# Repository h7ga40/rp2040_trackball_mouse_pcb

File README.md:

# PCB for Kensington trackball with RP2040

[Kensington Orbit Trackball with Scroll Ring](https://www.kensington.com/p/products/electronic-control-solutions/trackball-products/orbit-trackball-with-scroll-ring/)の基板を[PGA2040](https://shop.pimoroni.com/products/pga2040)を使っ基板に置き換えるためのKiCadプロジェクト

## 基板発注時の注意

板厚は**1.2mm**です。

## 主要部品

|部品|入手先|備考|
|-|-|-|
|PGA2040|<https://akizukidenshi.com/catalog/g/gM-16762/>|Raspberry pi picoと同じCPU|
|IR928-6C-F|<https://www.marutsu.co.jp/pc/i/12907560/>|ホイール用２相エンコーダのLED</br>見た目が同じなので選択|
|PT5529B/L2/H3|<https://www.marutsu.co.jp/pc/i/13719542/>|ホイール用２相エンコーダのフォトトランジスタ</br>見た目が同じなので選択|
|LMV393D|<https://www.marutsu.co.jp/pc/i/30637519/>|２相エンコーダ信号用のコンパレータ|
|B6B-PH-K-S|<https://www.marutsu.co.jp/pc/i/46628/>|ADNS-5050との接続用コネクタ|
|S5B-PH-K-S|<https://www.marutsu.co.jp/pc/i/54957/>|USBケーブルとの接続用コネクタ|
|kailh mute switch|<https://www.amazon.co.jp/s?k=kailh+mute+switch>|マウスボタン</br>[秋月のタクトスイッチ](https://akizukidenshi.com/catalog/g/gP-14892/)で代用（1.6mm(7.3mm-5.7mm)の底上げが必要）|
|タクトスイッチ|<https://akizukidenshi.com/catalog/g/gP-06184/>|RP2040のリセットとモード選択用|

## ソフトウェア

[こちら](https://github.com/h7ga40/rp2040_trackball_mouse)にソフトウェアがあります。

## 部品実装

PGA2040周辺はこのような感じ

## その他の情報

[コネクテッド・マウス](https://www.slideshare.net/HiroakiNagashima1/ss-250643168)

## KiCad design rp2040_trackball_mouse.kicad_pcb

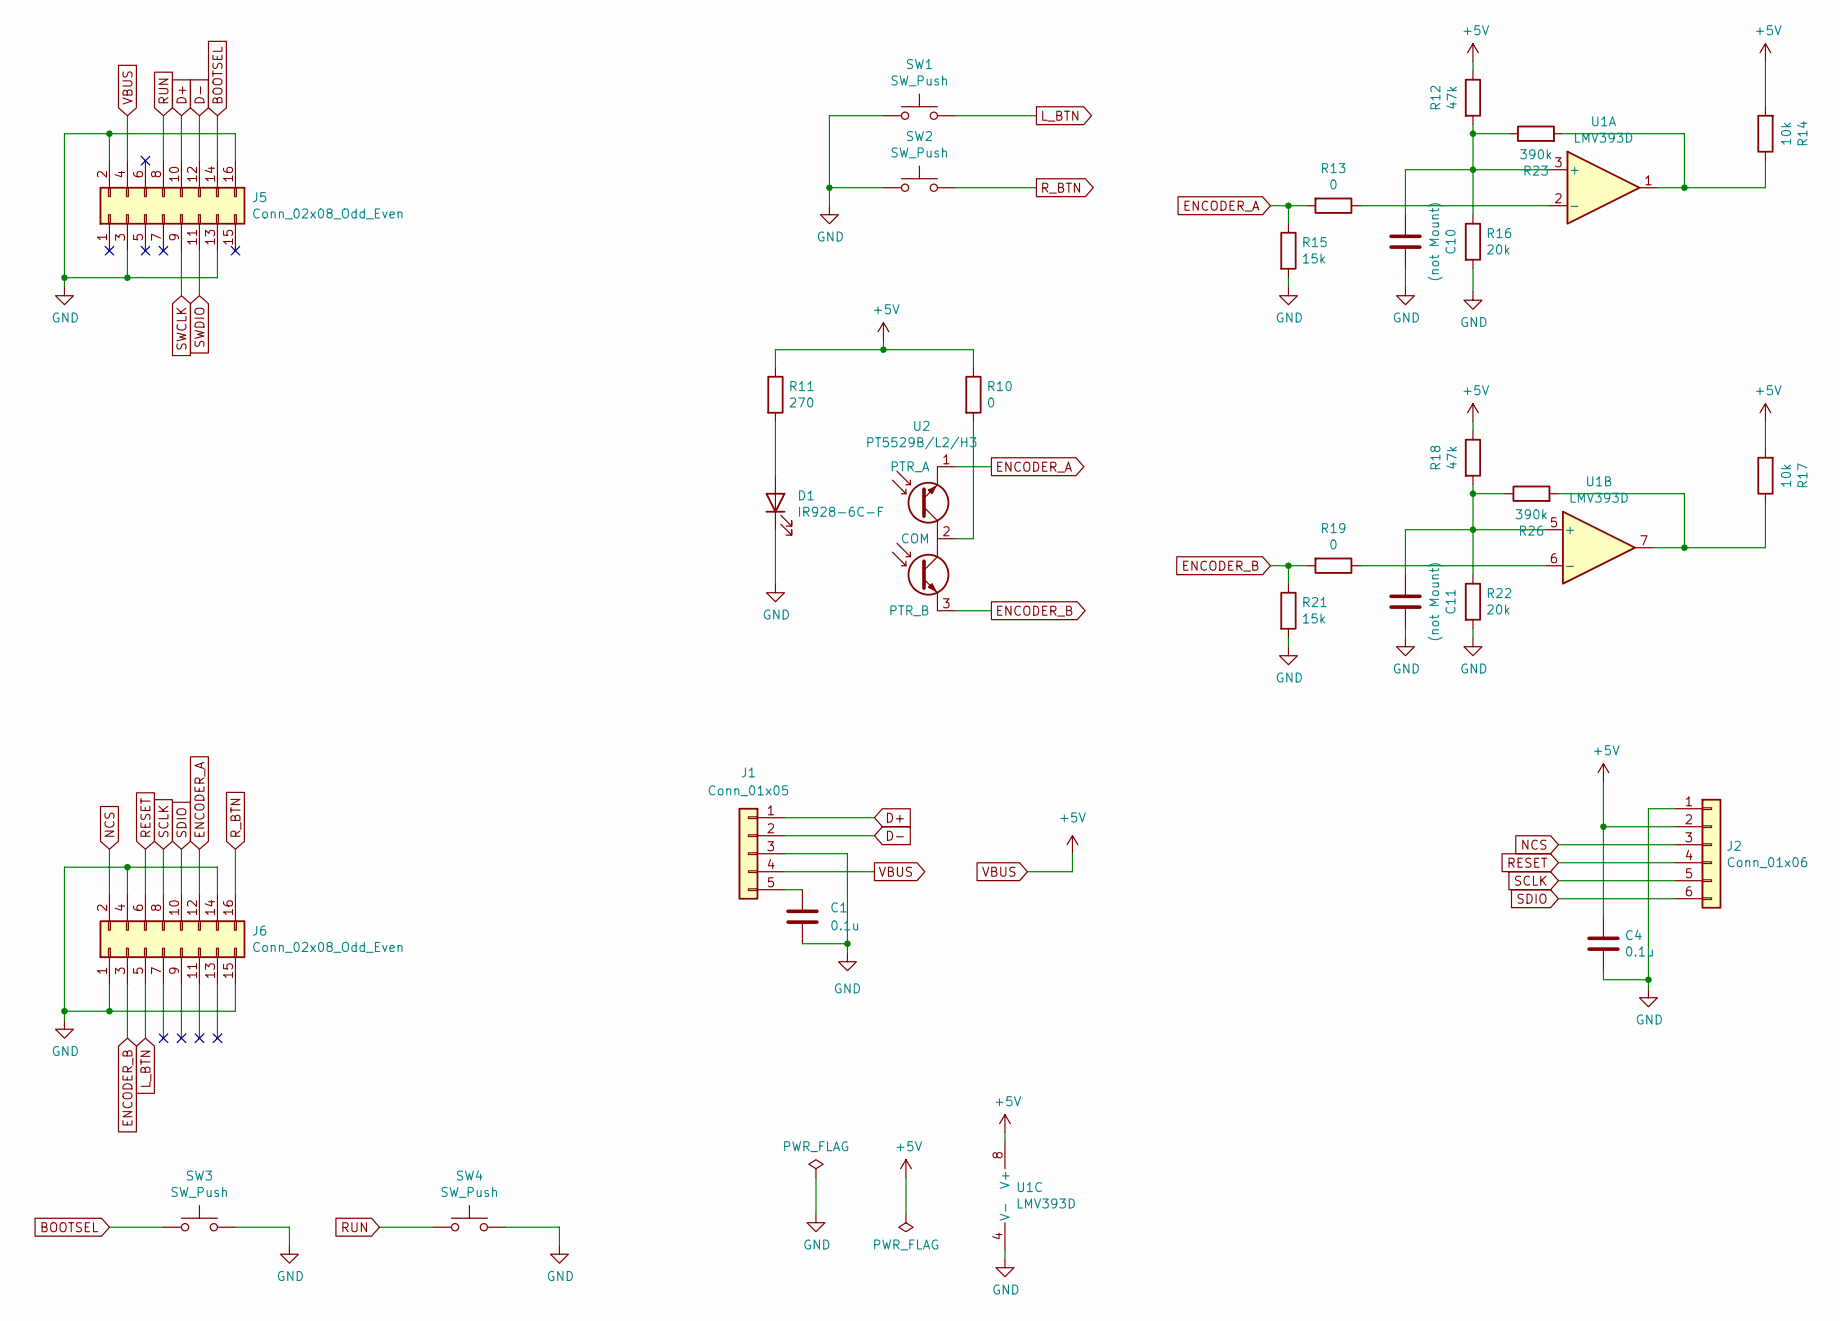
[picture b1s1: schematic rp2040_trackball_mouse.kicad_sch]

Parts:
C1, C4: 0.1u; C_0603_1608Metric_Pad1.08x0.95mm_HandSolder
C10, C11: (not Mount); C_0603_1608Metric_Pad1.08x0.95mm_HandSolder
D1: IR928-6C-F; LED_D2.0mm_W4.8mm_H2.5mm_FlatTop
J1: Conn_01x05; JST_PH_S5B-PH-K_1x05_P2.00mm_Horizontal
J2: Conn_01x06; JST_PH_B6B-PH-K_1x06_P2.00mm_Vertical
J5, J6: Conn_02x08_Odd_Even; PinHeader_2x08_P2.54mm_Vertical
R10, R13, R19: 0; R_0603_1608Metric_Pad0.98x0.95mm_HandSolder
R11: 270; R_0603_1608Metric_Pad0.98x0.95mm_HandSolder
R12, R18: 47k; R_0603_1608Metric_Pad0.98x0.95mm_HandSolder
R14, R17: 10k; R_0603_1608Metric_Pad0.98x0.95mm_HandSolder
R15, R21: 15k; R_0603_1608Metric_Pad0.98x0.95mm_HandSolder
R16, R22: 20k; R_0603_1608Metric_Pad0.98x0.95mm_HandSolder
R23, R26: 390k; R_0603_1608Metric_Pad0.98x0.95mm_HandSolder
SW1, SW2: SW_Push; CMI6273
SW3, SW4: SW_Push; SW_SPST_PTS810
U1: LMV393D; SOP-8_3.9x4.9mm_P1.27mm
U2: PT5529B/L2/H3; PinHeader_1x03_P2.54mm_Vertical

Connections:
BOOTSEL: J5.14, SW3.1
D+: J1.1, J5.10
D-: J1.2, J5.12
ENCODER_A: J6.12, R13.2, R15.1, U2.1 (PTR_A)
ENCODER_B: J6.3, R19.2, R21.1, U2.3 (PTR_B)
GND: C1.2, C4.2, C10.1, C11.2, D1.1 (K), J1.3, J2.1, J5.2, J5.3, J5.13, J5.16, J6.1, J6.4, J6.14, J6.15, R15.2, R16.2, R21.2, R22.2, SW1.1, SW2.1, SW3.2, SW4.2, U1.4 (V-)
L_BTN: J6.5, SW1.2
NCS: J2.3, J6.2
unnamed: C1.1, J1.5
unnamed: C10.2, R12.2, R16.1, R23.1, U1.3 (+)
unnamed: C11.1, R18.2, R22.1, R26.1, U1.5 (+)
unnamed: D1.2 (A), R11.2
unnamed: R10.2, U2.2 (COM)
unnamed: R13.1, U1.2 (-)
unnamed: R14.1, R23.2, U1.1
unnamed: R17.1, R26.2, U1.7
unnamed: R19.1, U1.6 (-)
RESET: J2.4, J6.6
RUN: J5.8, SW4.1
R_BTN: J6.16, SW2.2
SCLK: J2.5, J6.8
SDIO: J2.6, J6.10
SWCLK: J5.9
SWDIO: J5.11
VBUS: C4.1, J1.4, J2.2, J5.4, R10.1, R11.1, R12.1, R14.2, R17.2, R18.1, U1.8 (V+)

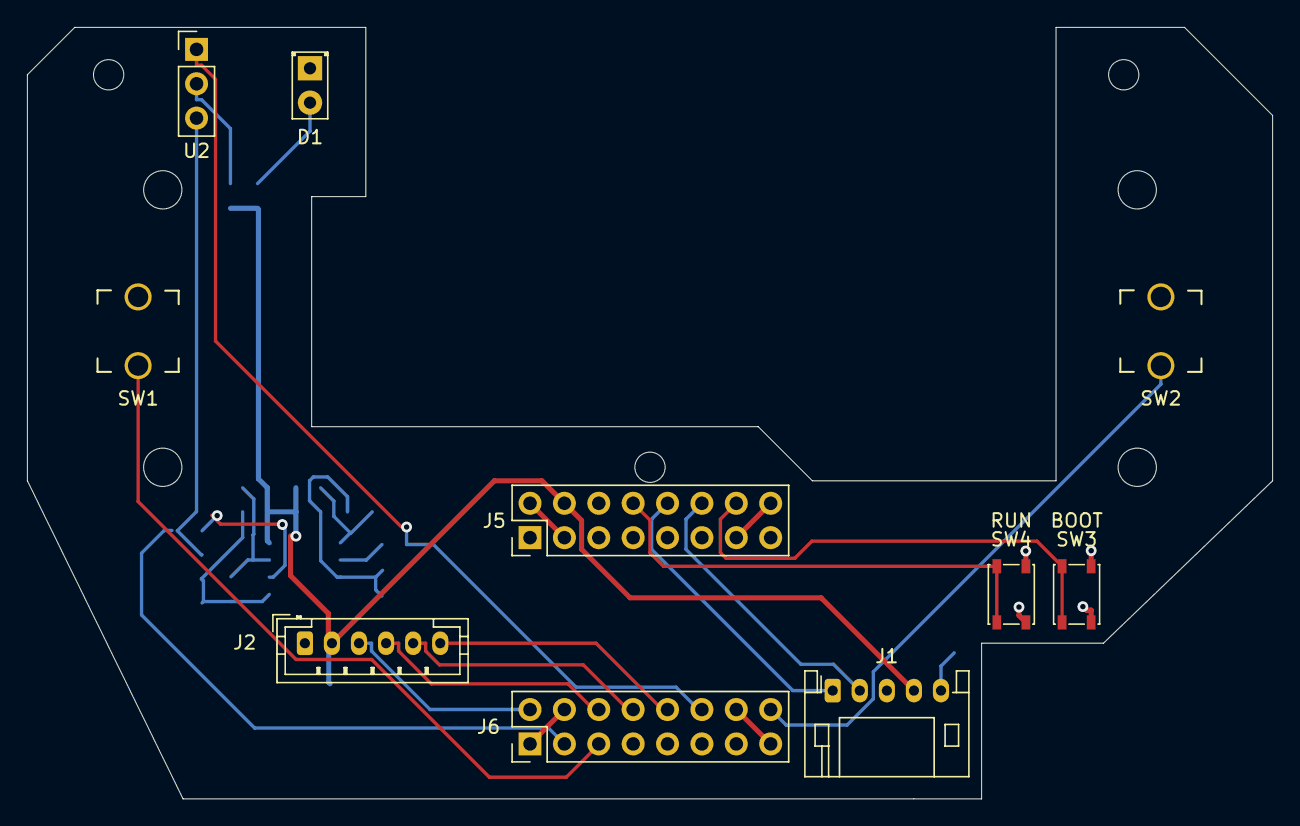
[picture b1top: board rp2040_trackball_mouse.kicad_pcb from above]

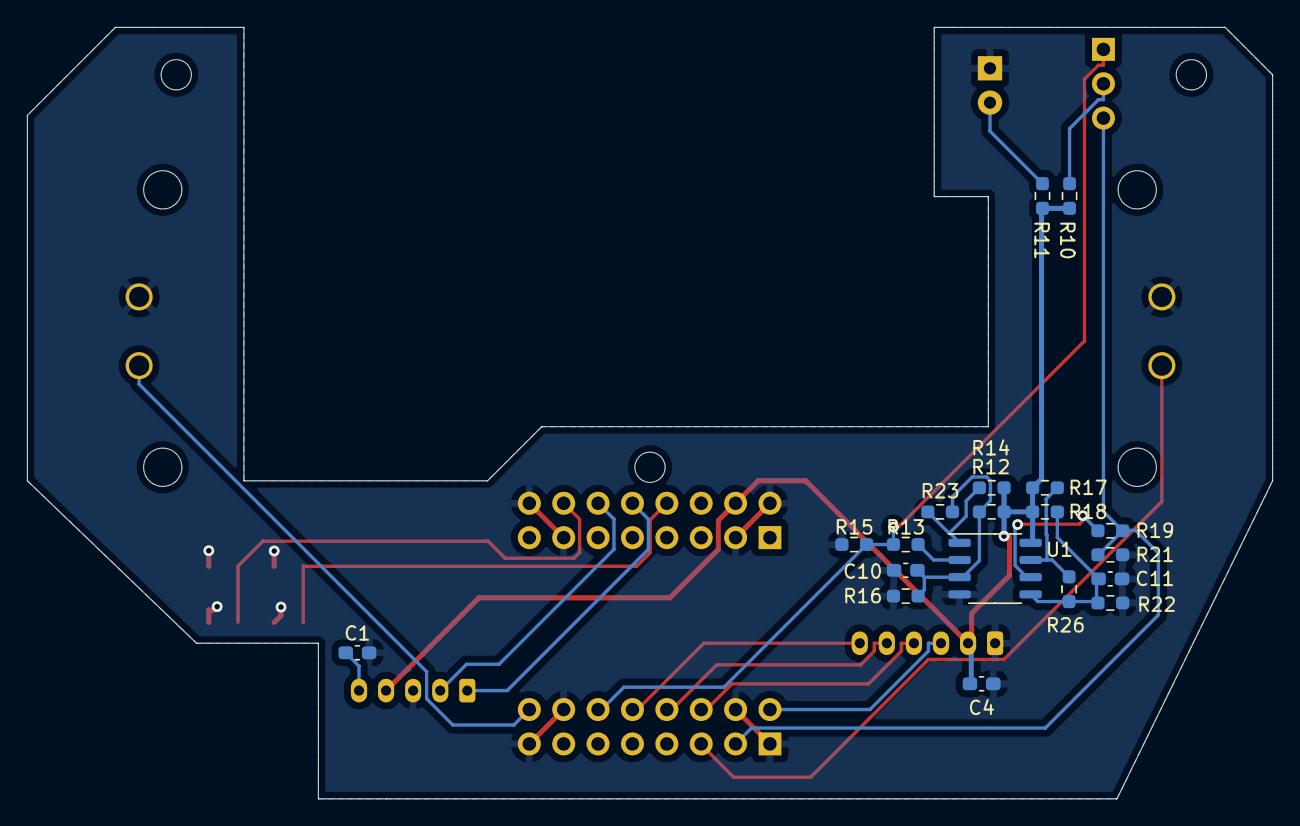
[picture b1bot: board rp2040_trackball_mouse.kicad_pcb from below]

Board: 2 copper layers, 92.0 x 57.0 mm, 29 parts (19 on the bottom side), 23 nets.

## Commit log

2022-11-23 ファイルを登録
2022-11-23 kicad_prlファイルを削除
2022-11-27 READMEを更新
2022-11-27 誤字を修正
2022-11-30 回路図を更新
2022-12-03 ホイールがぎこちないのを記述
2022-12-03 仮に入れていた値を削除
2022-12-03 ホイールの動作はGPIOをプルダウンして安定化したので記述削除
